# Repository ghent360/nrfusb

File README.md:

# Theory of operation #

A transmitter and receiver must be programmed with identical 32 bit
radio IDs.  With those IDs, the transmitter and receiver select a set of
23 channels using a pseudorandom number generator.

## Channel Selection ##

23 channels are selected.  Their selection and order is determined as
follows:

The pseudorandom number function is:

```
prn = (prn * 0x0019660D) + 0x3C6EF35F
```

A potential channel is `prn % 125`.  Channels are evaluated in order such that:

* The prn is evaluated once, then modulo 125 to generate a candidate
  channel

* No channel is repeated.  If the candidate channel has already been
  selected, the candidate is discarded.

* No more than a certain number of channels can be chosen from each of
  the different bands.  If a candidate channel would exceed this
  limit, it is discarded.
  * 0-31: 6
  * 32-63: 6
  * 64-95: 6
  * 96-125: 5

## Transmission ##

The transmitter and receiver use the nrf24l01 Enhanced ShockBurst with
the following parameters:

* 5 byte address field, the channel ID mapped into 5 bytes as below
* Dynamic payload length
* 2 byte CRC
* No automatic retransmission
* Auto acknowledgement
* 1Mbps data rate

The transmitter sends a new packet every 20ms, waiting 1ms for an
acknowledgement with data on the same channel.  Each transmitted
packet advances to the next channel in the channel selected list,
wrapping around.

## Reception ##

To initially lock onto a transmitter, the receiver picks a random
channel from the list and listens for 20 channel change times (0.4s).
If no packet is received, it then moves to the next channel in the
list and waits another 20 time periods, continuing this process until
a packet is received.  Once a packet is received it switches to the
following procedure.

In normal reception, immediately after receiving and acknowledging a
packet, the receiver switches to the next channel in the list.  It
waits at least 22ms for the next packet to be received.  If no packet
is received, then the channel is switched to the next one and
listening recommences.  If 5 packets in a row are missed, then the
receiver returns to the initial lock procedure.

## ID selection ##

The ShockBurst address is derived from the 32 bit ID as follows.

1100bbbb bbbbbbbH bbbbbbbH bbbbbbbH bbbbbbH

`b` is a bit from the 32 bit ID.

The `H` bits are selected to be the opposite of whatever the
preceeding bit was.

Rationale: The highest bits are defined to be distinct from the
preamble, which consists of alternating bits.  The H bits are present
to reduce the likelihood that random noise will cause the address to
be identified by the baseband receiver.

## Scheduling ##

The transmitter and receiver have 15 different "slots" to hold
outgoing data.  Each can be configured for a different priority or
transmission rate and each can hold up to 16 bytes of data.

The transmission rate/priority is configured by providing a 32 bit
bitmask denoting in which timeslots this slot should be sent.
Configuring an infeasible set of slots will result in unspecified data
being sent at a lower rate.

A priority of 0 is the default, which signifies that the slot should
not be transmitted.  0xffffffff implies it should be sent every
timeslot.  0x55555555 would be every other timeslot, etc.

The data in a slot will continue to be transmitted at the specified
frequency whether or not it has been updated by the client recently.

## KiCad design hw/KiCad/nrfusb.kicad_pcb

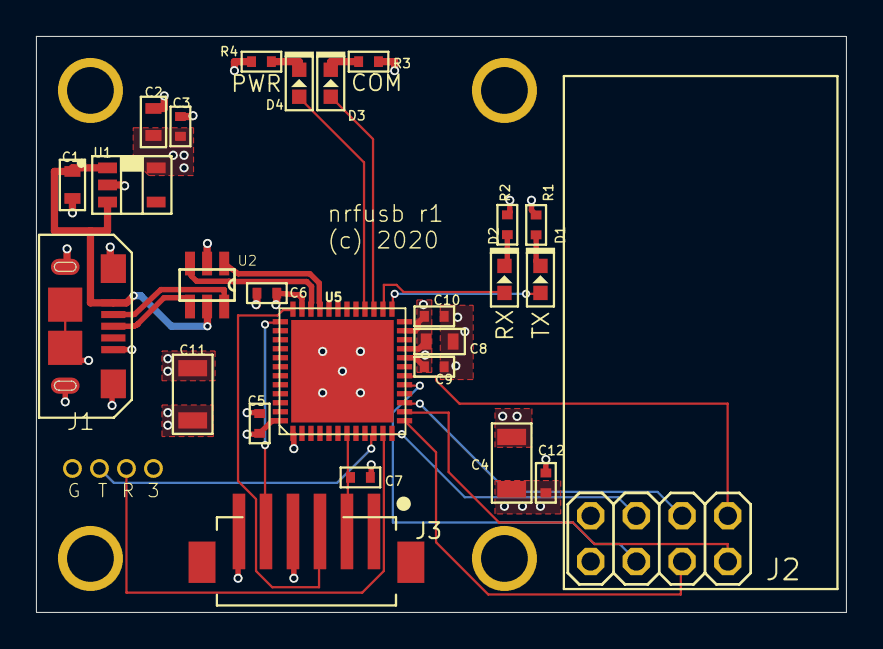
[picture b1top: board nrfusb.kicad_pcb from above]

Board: 4 copper layers, 45.0 x 32.0 mm, 34 parts (0 on the bottom side), 26 nets.

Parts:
C1, C2, C8: 1uF; C0603
C3, C5, C6, C7, C9, C10, C12: 0.1uF; C0402
C4, C11: 10uF; C1206
D1, D3: MF-LED-0603-GREEN; LED0603
D2, D4: MF-LED-0603-RED; LED0603
D3V0: PAD24AWG_PAD; 24AWG_PAD
DGND0: PAD24AWG_PAD; 24AWG_PAD
DRX0: PAD24AWG_PAD; 24AWG_PAD
DTX0: PAD24AWG_PAD; 24AWG_PAD
J1: MF-CON-MICROUSB-RIGHT; MICROUSB-RIGHT
J2: 2X04
J3: JST-ZH6SMT_VERT; JST_B6B-ZR-SM4-TF(LF)(SN)
M1, M2, M3, M4: MOUNT; M2.5MOUNT
R1, R2, R3, R4: 220; R0402
U1: MF-REG-SOT235-3.3V-300mA; SOT-23-5
U2: USBLC6-2SC6; SOT23-6L
U5: STM32G474CEU6; QFN50P700X700X60-49N

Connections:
+3V3: C2.P$1, C3.P$1, C4.P$1, C5.P$1, C6.P$1, C8.P$1, C9.P$1, C10.P$1, C11.P$1, C12.P$1, D3V0.P$1, J2.7, J3.6, U1.P$5, U5.1, U5.20, U5.21, U5.23, U5.35, U5.48
DEBUG_RX: DRX0.P$1, U5.11
DEBUG_TX: DTX0.P$1, U5.10
GND: C1.P$2, C2.P$2, C3.P$2, C4.P$2, C5.P$2, C6.P$2, C7.P$2, C8.P$2, C9.P$2, C10.P$2, C11.P$2, C12.P$2, DGND0.P$1, J1.5, J1.S1, J1.S2, J1.S3, J1.S4, J1.S5, J1.S6, J2.8, J3.4, R1.P$1, R2.P$1, R3.P$1, R4.P$1, U1.P$2, U2.2, U5.49
LED_COM: D3.ANODE, U5.27
LED_PWR: D4.ANODE, U5.28
LED_RF_RX: D2.ANODE, U5.26
LED_RF_TX: D1.ANODE, U5.25
unnamed: D1.CATHODE, R1.P$2
unnamed: D2.CATHODE, R2.P$2
unnamed: D3.CATHODE, R3.P$2
unnamed: D4.CATHODE, R4.P$2
NRF_CE: J2.6, U5.17
NRF_CS: J2.5, U5.12
NRF_IRQ: J2.1, U5.18
NRF_MISO: J2.2, U5.14
NRF_MOSI: J2.3, U5.15
NRF_SCK: J2.4, U5.13
NRST: C7.P$1, J3.2, U5.7
SWCLK: J3.5, U5.37
SWDIO: J3.3, U5.36
USB_D_N: J1.2, U2.6
USB_D_P: J1.3, U2.4
USB_F_N: U2.1, U5.33
USB_F_P: U2.3, U5.34
VBUS: C1.P$1, J1.1, U1.P$1, U1.P$3, U2.5

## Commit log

2019-10-08 Initialize with a fork of fdcanusb
2019-10-08 Nominally complete board and schematic
2020-02-18 Update with correct stm32 pinout
2020-02-18 Auto-route
2020-02-18 Remove an autogenerated file
2020-02-18 Fine tweak silks
2020-03-06 Stub firmware
2020-03-07 Change the USB name and stub in USB CDC support
2020-03-07 Configure the nrf on power up
2020-03-07 Basic NRF operations (not seeming to work yet)
2020-03-07 Make flash.sh actually work
2020-03-07 Basic operation without automatic ack working
    There are probably some things can be simplified back still.
2020-03-09 Get things besides auto-ack working
2020-03-12 Add nrf24l01+ datasheet
2020-03-12 Auto-ack works with bidirectional data!
2020-03-13 Update TODO
2020-03-16 Support online channel selection
2020-03-16 Refactor pin configuration to enable direct pass through
2020-03-17 Beginnings of the slot protocol implementation
2020-03-17 Actually look in the correct place for sources
2020-03-17 First draft of an interface and misc bug fixes
    This currently has raw vs. slot selected at compile time. It also
    doesn't work properly yet, but does transmit "something".
2020-03-18 Fix enough bugs to get sending and receiving working
2020-03-18 Set SPI frequency to 10MHz
2020-03-18 Use the correct frequency for the millisecond timer
2020-03-18 No longer die for errors
2020-03-18 Make parsing of slots greater than 0 actually work
2020-03-18 Get priority selection working and fix other bugs
2020-04-01 Add a udev rule
2020-04-30 Factor to be closer to supporting multiple receivers
    At the moment, still only one remote is supported though
2020-04-30 Actually support transmitting to multiple receivers
    Also, add a transmit timeout. At least some transmission must occur
    every N ms or all of the channels get their priority set to 0.
2020-04-30 Fix a race when associating remotes
    If the response from a remote came in after more than 1ms, it would be
    associated with the next remote.
2022-12-28 Update libusb_stm32 to the latest version. Make code compile for STM32F4.
2022-12-28 Fix issues with no NRF module connected.
2022-12-28 Add file to initialize the USB pins on STM32F4.
2022-12-28 Comment on the disabled code.
2022-12-28 Add KiCAD schematics and PCB, fix clock source for the F4 board.
2022-12-28 Switch to my copy of rules_mbed.
2022-12-28 Update to my most recent version of rbed_rules. Update bazel version. Update mjlib version. Fix build issues.
2022-12-28 Fix STM32F1 compile issues. Sadly the binary is too big for the bluepill.
2022-12-28 Update NRF module pins.
